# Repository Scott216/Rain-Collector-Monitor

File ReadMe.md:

Rain Collector

Outside board is panStamp plugged into a PCB which monitors temp of two heating pads, temp inside rain collector and temp below rain collector.  It also monitors pulses from rain collector and closes a relay for every pulse for the Davis Weather station.  Data is wirelessly sent to the panStamp on the inside.  The outside unit also turns on the heaters to melt the snow.  If outside temp is below freezing, heaters will come on for a few minutes.  If nothing melts to trip the water paddle, then heaters will turn off for a while.  If water is detected, heaters will stay on until all snow is melted.

The inside panStamp is connected to an Ethernet module which posts the data on Xively.
https://xively.com/feeds/103470/

As of 12/17/14 - the Rx sketch is compiled on Arduino IDE 1.5.8.  Some of the libraries need to be modified so the Ethernet SS pin can be assigned to a pin other then D10, because panStamp uses D10 to communicate with the radio.  The Tx sketch on the other hand is still compiled with Arduino 1.0.5, but needs to be updated to 1.5.8.

See [Arduino forum thread](http://forum.arduino.cc/index.php?topic=217423.msg1962182#msg1962182) and files regarding changing SS pin:

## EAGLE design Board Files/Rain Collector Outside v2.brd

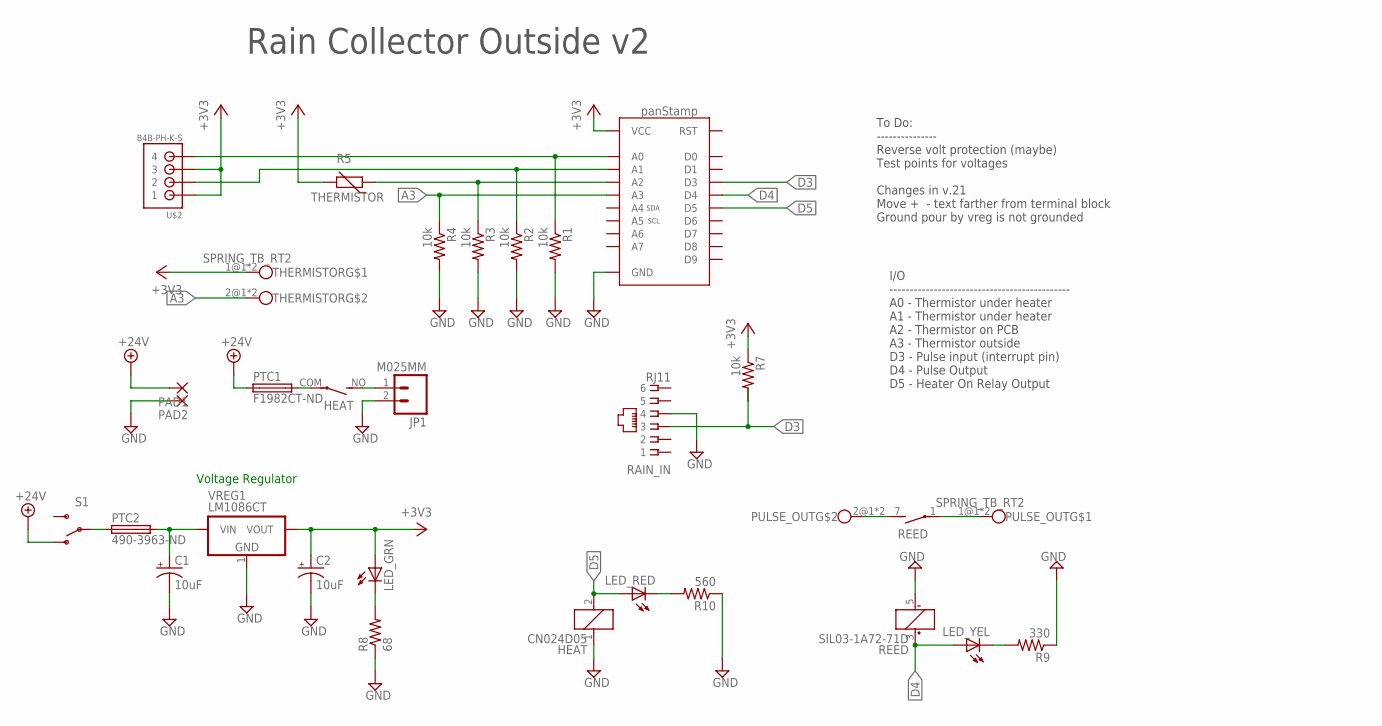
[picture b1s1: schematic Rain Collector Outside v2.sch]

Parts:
C1, C2: 10uF; CPOL-RADIAL-10UF-25V; PARTNO 478-6062-ND
HEAT: CN024D05; APF30212A; PARTNO CC1742-ND
JP1: M025MM; SCREWTERMINAL-5MM-2; PARTNO Sparkfun PRT-08432
LED_GRN: LED3MM
LED_RED: LED3MM
LED_YEL: LED3MM
PAD1, PAD2: 3,17/1,3
PANSTAMP: PANSTAMPNO_TEXT; PANSTAMP_NOTEXT
PTC1: F1982CT-ND; TE5; PARTNO F1982CT-ND
PTC2: 490-3963-ND; TE5; PARTNO 490-3963-ND
PULSE_OUT: SPRING_TB_RT2; PARTNO Sprakfun PRT-08073
R1, R2, R3, R4, R7: 10k; AXIAL-0.3; PARTNO RNF18FTD10K0CT-ND
R5: THERMISTOR; RS-2,5; PARTNO BC2301-ND
R8: 68; AXIAL-0.3; PARTNO CF18JT68R0CT-ND
R9: 330; AXIAL-0.3; PARTNO CF18JT330RCT-ND
R10: 560; AXIAL-0.3; PARTNO CF18JT560RCT-ND
RAIN_IN: RJ11; RJ11-NO_SHIELD; PARTNO A31406-ND
REED: SIL03-1A72-71D; REED; PARTNO 374-1322-ND
S1: SWITCH-SPDTPTH; SWITCH-SPDT; PARTNO EG1903-ND
THERMISTOR: SPRING_TB_RT2; PARTNO Sparkfun PRT-08073
U$2: B4B-PH-K-S; JST_B4B-PH_HEADER; PARTNO 455-1706-ND
VREG1: LM1086CT; TO-220V

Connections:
+3V3: C2.1 (+), LED_GRN.A, PANSTAMP.VCC, R5.2, R7.P$1 (1), THERMISTOR.1@1, THERMISTOR.1@2, U$2.P1 (1), U$2.P3 (3), VREG1.2 (VOUT)
+24V: PAD1.1, PTC1.1, S1.1 (O)
A0: PANSTAMP.A0, R1.P$1 (1), U$2.P4 (4)
A1: PANSTAMP.A1, R2.P$1 (1), U$2.P2 (2)
A2: PANSTAMP.A2, R3.P$1 (1), R5.1
A3: PANSTAMP.A3, R4.P$1 (1), THERMISTOR.2@1, THERMISTOR.2@2
D3: PANSTAMP.D3, R7.P$2 (2), RAIN_IN.3
D4: LED_YEL.A, PANSTAMP.D4, REED.3 (+)
D5: HEAT.2, LED_RED.A, PANSTAMP.D5
GND: C1.2 (-), C2.2 (-), HEAT.1, JP1.2, PAD2.1, PANSTAMP.GND$1 (GND), PANSTAMP.GND$7 (GND), PANSTAMP.GND$15 (GND), PANSTAMP.GND$23 (GND), PANSTAMP.GND$24 (GND), R1.P$2 (2), R2.P$2 (2), R3.P$2 (2), R4.P$2 (2), R8.P$1 (1), R9.P$1 (1), R10.P$1 (1), RAIN_IN.4, REED.5 (-), VREG1.1 (GND)
unnamed: PULSE_OUT.2@1, PULSE_OUT.2@2, REED.7 (S)
unnamed: PULSE_OUT.1@1, PULSE_OUT.1@2, REED.1
unnamed: HEAT.NO (S), JP1.1
unnamed: LED_GRN.K (C), R8.P$2 (2)
unnamed: LED_YEL.K (C), R9.P$2 (2)
unnamed: LED_RED.K (C), R10.P$2 (2)
unnamed: PTC2.1, S1.2
unnamed: C1.1 (+), PTC2.2, VREG1.3 (VIN)
unnamed: HEAT.COM, PTC1.2

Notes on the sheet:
I/O --------------------------------------------- A0 - Thermistor under heater A1 - Thermistor under heater A2 - Thermistor on PCB A3 - Thermistor outside D3 - Pulse input (interrupt pin) D4 - Pulse Output D5 - Heater On Relay Output
Voltage Regulator
To Do: --------------- Reverse volt protection (maybe) Test points for voltages Changes in v.21 Move + - text farther from terminal block Ground pour by vreg is not grounded
Rain Collector Outside v2

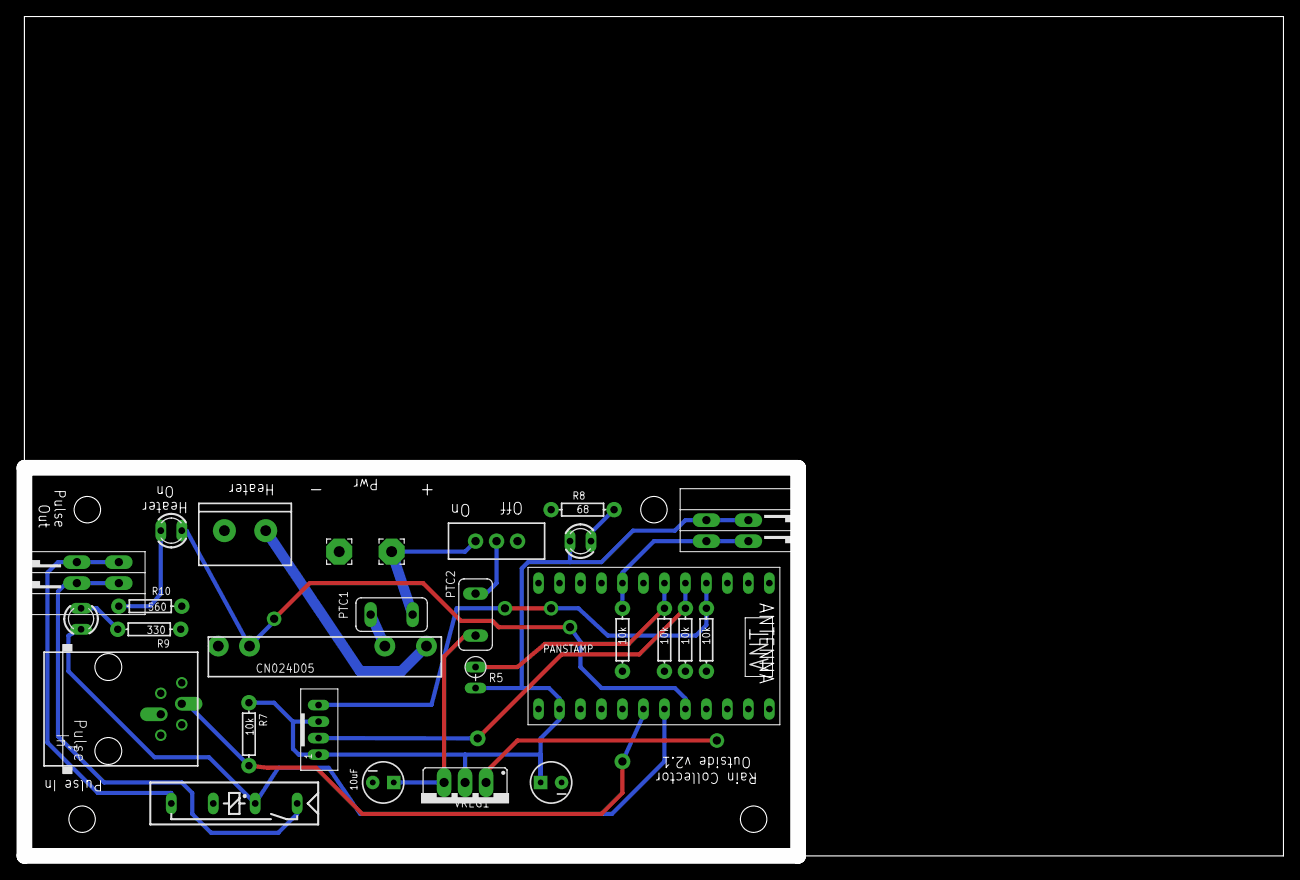
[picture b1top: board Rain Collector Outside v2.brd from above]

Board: 2 copper layers, 152.4 x 101.6 mm, 28 parts (0 on the bottom side), 19 nets.

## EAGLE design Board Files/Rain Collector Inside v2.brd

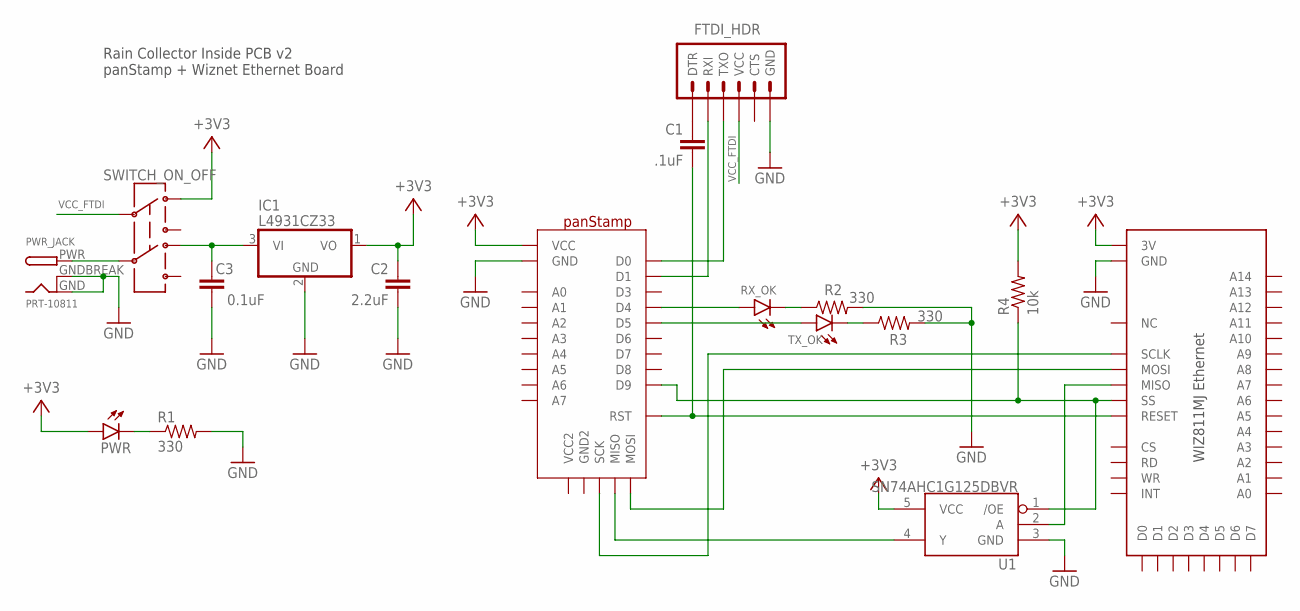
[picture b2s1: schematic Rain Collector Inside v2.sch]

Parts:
C1: .1uF; CAP-PTH-5MM
C2: 2.2uF; CAP-PTH-5MM
C3: 0.1uF; CAP-PTH-5MM
FTDI_HDR: ARDUINO_SERIAL_PROGRAMLONGPADS; 1X06_LONGPADS
IC1: L4931CZ33; TO92
PANSTAMP: PANSTAMP_SPI
PWR: LED5MM
PWR_JACK: PRT-10811; DCJACK_2MM_PTH
R1, R2, R3: 330; AXIAL-0.4
R4: 10k; AXIAL-0.4
RX_OK: LED5MM
SWITCH_ON_OFF: 401-2001-ND; SWITCH_DPDT_PTH
TX_OK: LED5MM
U1: SN74AHC1G125DBVR; SOT23-5
U$2: WIZ811MJ

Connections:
+3V3: C2.1, IC1.1 (VO), PANSTAMP.VCC, PWR.A, R4.P$2 (2), SWITCH_ON_OFF.1, U1.5 (VCC), U$2.3V@1 (3V), U$2.3V@2 (3V)
DTR: C1.1, FTDI_HDR.1 (DTR)
GND: C2.2, C3.2, FTDI_HDR.6 (GND), IC1.2 (GND), PANSTAMP.GND$1 (GND), PANSTAMP.GND$7 (GND), PANSTAMP.GND$15 (GND), PANSTAMP.GND$23 (GND), PANSTAMP.GND$24 (GND), PWR_JACK.GND, PWR_JACK.GNDBREAK, R1.P$2 (2), R2.P$2 (2), R3.P$2 (2), U1.3 (GND), U$2.GND@1 (GND), U$2.GND@2 (GND), U$2.GND@3 (GND), U$2.GND@4 (GND), U$2.GND@5 (GND)
GND2: PANSTAMP.GND2
MISO: PANSTAMP.MISO, U1.4 (Y)
MOSI: PANSTAMP.MOSI, U$2.MOSI
unnamed: FTDI_HDR.3 (TXO), PANSTAMP.D0
unnamed: FTDI_HDR.2 (RXI), PANSTAMP.D1
unnamed: PWR_JACK.PWR, SWITCH_ON_OFF.5
unnamed: PWR.K (C), R1.P$1 (1)
unnamed: U1.2 (A), U$2.MISO
unnamed: R2.P$1 (1), RX_OK.K (C)
unnamed: R3.P$1 (1), TX_OK.K (C)
unnamed: C3.1, IC1.3 (VI), SWITCH_ON_OFF.4
RST: C1.2, PANSTAMP.RESET (RST), U$2.RESET
RXLED: PANSTAMP.D4, RX_OK.A
SCLK: PANSTAMP.SCK, U$2.SCLK
SS: PANSTAMP.D9, R4.P$1 (1), U1.1 (/OE), U$2.SCS (SS)
TXLED: PANSTAMP.D5, TX_OK.A
VCC2: PANSTAMP.VCC2
VCC_FTDI: FTDI_HDR.4 (VCC), SWITCH_ON_OFF.2

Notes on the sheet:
Rain Collector Inside PCB v2 panStamp + Wiznet Ethernet Board

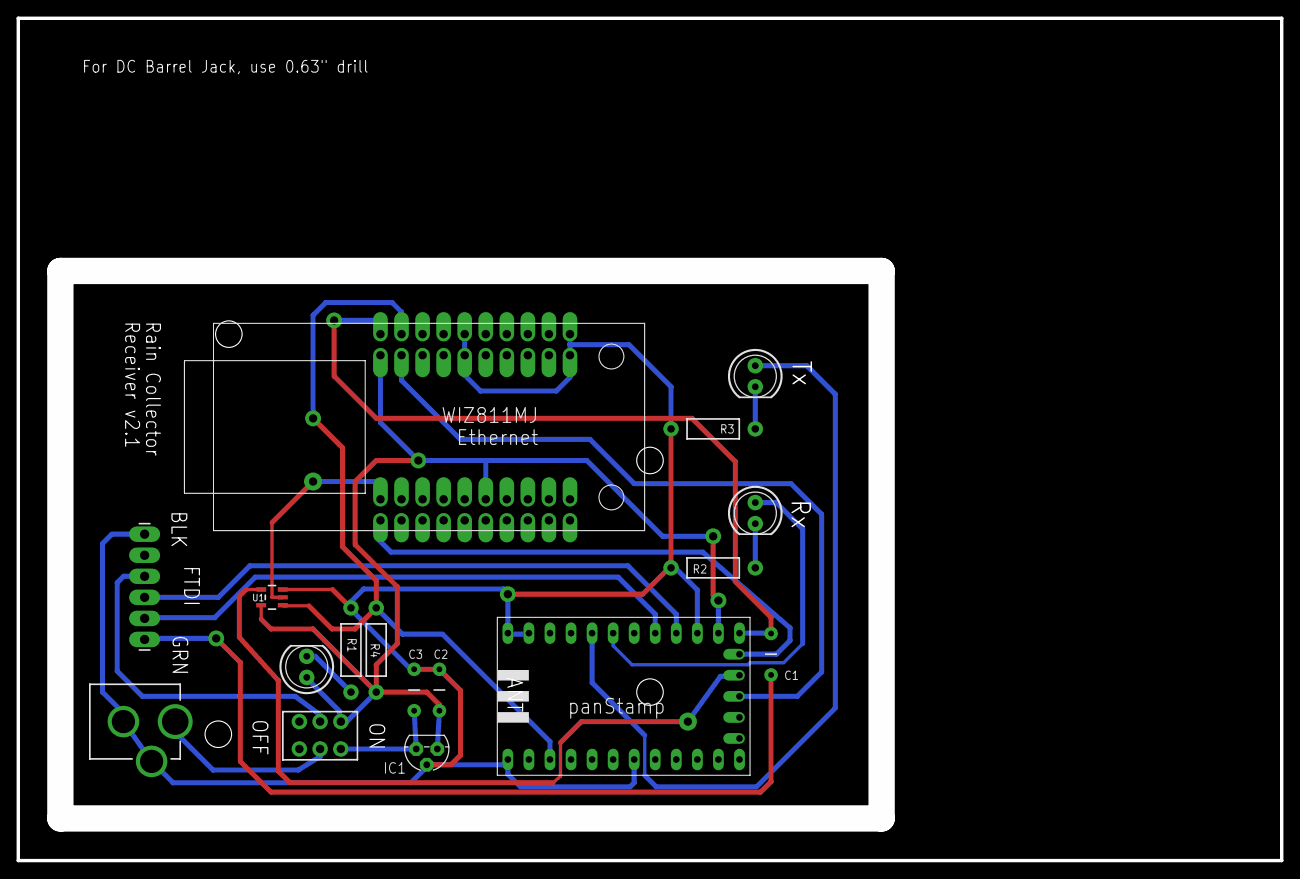
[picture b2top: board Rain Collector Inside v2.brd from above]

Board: 2 copper layers, 152.4 x 101.6 mm, 17 parts (0 on the bottom side), 19 nets.

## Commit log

2014-12-18 Added info about IDE and modified libraries
2014-12-18 Eagle Board Files
    Used Eagle 7.1. Outside PCB was made by fab house, Inside PCB was made
    by me on Shapeoko
2014-12-25 v0.14 added high power setting
2015-01-04 Changes to comments
2015-02-04 v2.06 - added Rx status channel
    Added Good/Bad status indicating if inside panStamp was receiving data.
    Did this so I could setup a Xively-Zapier trigger when inside panStamp
    wasn’t getting any data. Seems to happen when there is snow on the
    deck.
    Reformatted the change log.
2015-02-28 v0.15 changed heating time
    Increased heater on time to 40 min if temp is < 20 degrees. Renamed
    some variables
2015-03-07 v2.08 Added RSSI
2015-03-07 v2.01 - upgraded to API
    Re-wrote sketch to use latest panStamp API

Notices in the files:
parts and their libraries:
SparkFun-Connectors: Licensing: Creative Commons ShareAlike 4.0 International - https://creativecommons.org/licenses/by-sa/4.0
SparkFun-Connectors: Licensing: CC v3.0 Share-Alike You are welcome to use this library for commercial purposes.
